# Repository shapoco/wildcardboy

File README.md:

# [WIP] WildCardBoy

Handheld Game Console with Replaceable MCU

## Concept

WildCardBoy is a handheld game console whose "brain" (MCU) can be swapped out.
It consists of two units:

- **Host shell**: The main unit with an LCD, keypad, TF card slot, and power supply.
  It has no game-execution capability of its own; instead, it has a slot for a logic card on its back.
- **Logic card**: A daughterboard that plugs into the slot. It carries the MCU that runs the game,
  along with the CPU peripheral circuitry of the target game console (e.g. TinyJoypad, Arduboy).

The differences between game consoles are confined to the logic card,
so supporting a new game console only requires building a new logic card.

The host shell acts as an RP2350B-based host controller with the following roles:

- Detecting the logic card and identifying its type via the on-card EEPROM (card profile)
- Reading keypad input and sending it to the logic card
- Driving the LCD based on drawing commands received from the logic card
- Flashing game programs stored on the TF card to the MCU on the logic card

For detailed specifications, see [spec/](spec/).

For demos and the latest development status, see the [#WildCardBoy tag on X](https://x.com/hashtag/WildCardBoy?f=live).

## Schematics

[host_shell.kicad_sch](https://kicanvas.org/?repo=https://github.com/shapoco/wildcardboy/blob/main/kicad/host_shell.kicad_sch)

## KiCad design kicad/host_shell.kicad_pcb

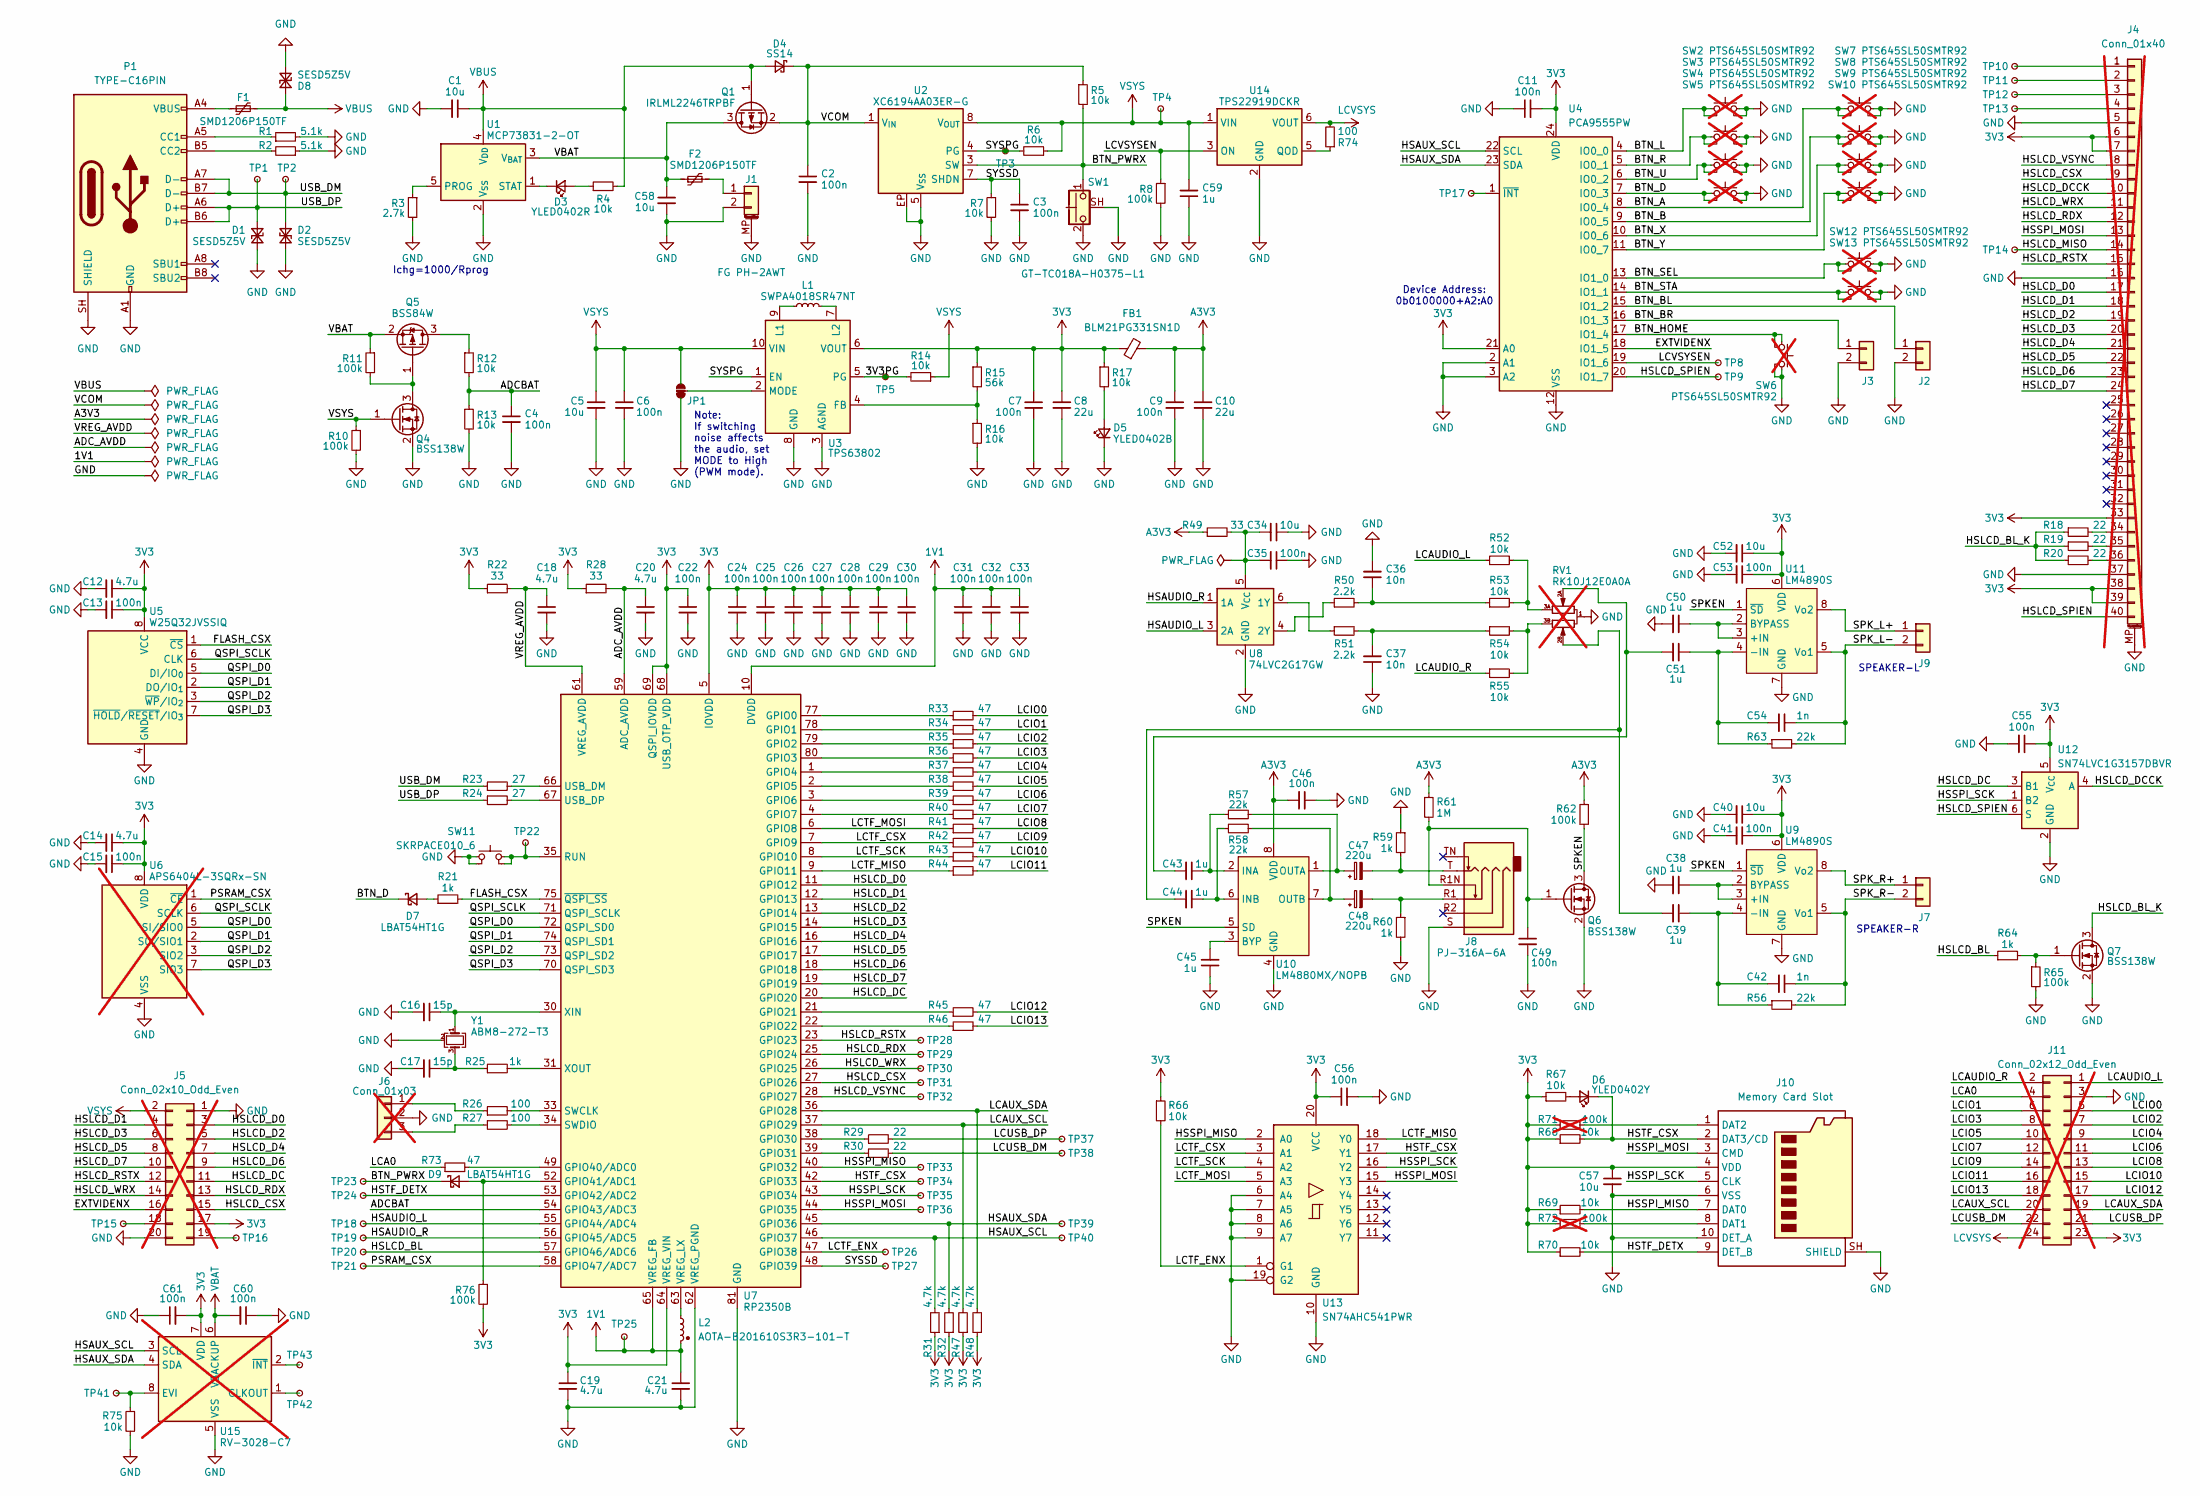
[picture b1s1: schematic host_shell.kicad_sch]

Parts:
C1, C5, C34, C40, C52, C57, C58: 10u; C_0603_1608Metric; LCSC C1691
C2, C3, C4, C6, C7, C9, C11, C13, C15, C22, C24, C25, C26, C27, C28, C29, C30, C31, C32, C33, C35, C41, C46, C49, C53, C55, C56, C60, C61: 100n; C_0402_1005Metric; LCSC C1525
C8, C10: 22u; C_0603_1608Metric; LCSC C59461
C12, C14, C18, C19, C20, C21: 4.7u; C_0603_1608Metric; LCSC C19666
C16, C17: 15p; C_0402_1005Metric; LCSC C1548
C36, C37: 10n; C_0402_1005Metric; LCSC C15195
C38, C39, C43, C44, C45, C50, C51, C59: 1u; C_0402_1005Metric; LCSC C52923
C42, C54: 1n; C_0402_1005Metric; LCSC C1523
C47, C48: 220u; CP_Elec_6.3x5.4; LCSC C3345
D1, D2, D8: SESD5Z5V; D_SOD-523; LCSC C19631222
D3: YLED0402R; LED_0402_1005Metric_Pad0.77x0.64mm_HandSolder; LCSC C21260817
D4: SS14; D_SMA; LCSC C2480
D5: YLED0402B; LED_0402_1005Metric_Pad0.77x0.64mm_HandSolder; LCSC C30584803
D6: YLED0402Y; LED_0402_1005Metric_Pad0.77x0.64mm_HandSolder; LCSC C20608782
D7, D9: LBAT54HT1G; D_SOD-323; LCSC C12744
F1, F2: SMD1206P150TF; Fuse_1206_3216Metric; LCSC C20802
FB1: BLM21PG331SN1D; L_0805_2012Metric; LCSC C74764
J1: FG PH-2AWT; JST_PH_S2B-PH-SM4-TB_1x02-1MP_P2.00mm_Horizontal; LCSC C2763693
J2, J3: Conn_01x02; SolderWirePad_1x02_SMD_2.5x1.5mm
J4: Conn_01x40; FFC_Conn_40P_Top_Hand; not fitted
J5: Conn_02x10_Odd_Even; PinSocket_2x10_P2.54mm_Horizontal; not fitted
J6: Conn_01x03; PinHeader_1x03_P2.54mm_Vertical; not fitted
J7, J9: Conn_01x02; SolderWirePad_2x01_SMD_2.5x1.5mm
J8: PJ-316A-6A; Jack_3.5mm_PJ-316A-6A_Horizontal; LCSC C128987
J10: Memory Card Slot; microSD_HC_Hirose_DM3AT-SF-PEJM5; LCSC C114218
J11: Conn_02x12_Odd_Even; PinSocket_2x12_P2.54mm_Horizontal; not fitted
JP1: SolderJumper_3_Bridged12; SolderJumper-3_P1.3mm_Bridged12_RoundedPad1.0x1.5mm
L1: SWPA4018SR47NT; L_Sunlord_SWPA4018S; LCSC C527613
L2: AOTA-B201610S3R3-101-T; LCSC C42411119
P1: TYPE-C16PIN; USB_C_Receptacle_HCTL_HC-TYPE-C-16P-01A; LCSC C393939
Q1: IRLML2246TRPBF; SOT-23; LCSC C127272
Q4, Q6, Q7: BSS138W; SOT-323_SC-70; LCSC C504052
Q5: BSS84W; SOT-323_SC-70; LCSC C919394
R1, R2: 5.1k; R_0402_1005Metric; LCSC C25905
R3: 2.7k; R_0402_1005Metric; LCSC C25885
R4, R5, R6, R7, R12, R13, R14, R16, R17, R52, R53, R54, R55, R66, R67, R68, R69, R70, R75: 10k; R_0402_1005Metric; LCSC C25744
R8, R10, R11, R62, R65, R76: 100k; R_0402_1005Metric; LCSC C25741
R15: 56k; R_0402_1005Metric; LCSC C25567
R18, R19, R20, R29, R30: 22; R_0402_1005Metric; LCSC C25092
R21, R25, R59, R60, R64: 1k; R_0402_1005Metric; LCSC C11702
R22, R28, R49: 33; R_0402_1005Metric; LCSC C25105
R23, R24: 27; R_0402_1005Metric; LCSC C25100
R26, R27, R74: 100; R_0402_1005Metric; LCSC C25076
R31, R32, R47, R48: 4.7k; R_0402_1005Metric; LCSC C25900
R33, R34, R35, R36, R37, R38, R39, R40, R41, R42, R43, R44, R45, R46, R73: 47; R_0402_1005Metric; LCSC C25118
R50, R51: 2.2k; R_0402_1005Metric; LCSC C25879
R56, R57, R58, R63: 22k; R_0402_1005Metric; LCSC C25768
R61: 1M; R_0402_1005Metric; LCSC C26083
R71, R72: 100k; R_0402_1005Metric; LCSC C25741; not fitted
RV1: RK10J12E0A0A; RK10J1xE; LCSC C351176; not fitted
SW1: GT-TC018A-H0375-L1; LCSC C963235
SW2, SW3, SW4, SW5, SW6, SW7, SW8, SW9, SW10, SW12, SW13: PTS645SL50SMTR92; SW_SPST_PTS645Sx43SMTR92; not fitted
SW11: SKRPACE010_6; SW_Push_1P1T_NO_Vertical_Wuerth_434133025816; LCSC C139797
TP1, TP2, TP3, TP4, TP5, TP8, TP9, TP10, TP11, TP12, TP13, TP14, TP15, TP16, TP17, TP18, TP19, TP20, TP21, TP22, TP23, TP24, TP25, TP26, TP27, TP28, TP29, TP30, TP31, TP32, TP33, TP34, TP35, TP36, TP37, TP38, TP39, TP40, TP41, TP42, TP43: TestPoint_Small; TestPoint_Pad_D1.0mm
U1: MCP73831-2-OT; SOT-23-5; LCSC C14879
U2: XC6194AA03ER-G; USP-8B06; LCSC C18221112
U3: TPS63802; LCSC C2845237
U4: PCA9555PW; TSSOP-24_4.4x7.8mm_P0.65mm; LCSC C128392
U5: W25Q32JVSSIQ; SOIC-8_5.3x5.3mm_P1.27mm; LCSC C179173
U6: APS6404L-3SQRx-SN; SOP-8_3.76x4.96mm_P1.27mm; not fitted
U7: RP2350B; QFN-80-1EP_10x10mm_P0.4mm_EP3.4x3.4mm; LCSC C42415655
U8: 74LVC2G17GW; SOT-363_SC-70-6; LCSC C19829576
U9, U11: LM4890S; MSOP-8_3x3mm_P0.65mm; LCSC C329452
U10: LM4880MX/NOPB; SOIC-8_3.9x4.9mm_P1.27mm; LCSC C2872533
U12: SN74LVC1G3157DBVR; SOT-23-6; LCSC C10426
U13: SN74AHC541PWR; TSSOP-20_4.4x6.5mm_P0.65mm; LCSC C406865
U14: TPS22919DCKR; SOT-363_SC-70-6; LCSC C2149796
U15: RV-3028-C7; MicroCrystal_C7_SON-8_1.5x3.2mm_P0.9mm; LCSC C3304278; not fitted
Y1: ABM8-272-T3; Crystal_SMD_3225-4Pin_3.2x2.5mm; LCSC C20625731

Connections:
1V1: C21.1, C31.1, C32.1, C33.1, L2.1, TP25.1 (1_1), U7.10 (DVDD), U7.32 (DVDD), U7.51 (DVDD), U7.65 (VREG_FB)
3V3: C7.1, C8.1, C11.2, C12.1, C13.1, C14.1, C15.1, C19.1, C22.1, C24.1, C25.1, C26.1, C27.1, C28.1, C29.1, C30.1, C40.1, C41.1, C52.1, C53.1, C55.1, C56.1, C57.1, C61.2, FB1.1, J4.6, J4.7, J4.33, J4.38, J4.39, J5.17, J10.4 (VDD), J11.23, R15.1, R17.1, R22.1, R28.1, R31.1, R32.1, R47.1, R48.1, R66.1, R67.1, R68.1, R69.1, R70.1, R71.1, R72.1, R76.2, U3.6 (VOUT), U4.21 (A0), U4.24 (VDD), U5.8 (VCC), U6.8 (VDD), U7.5 (IOVDD), U7.15 (IOVDD), U7.24 (IOVDD), U7.29 (IOVDD), U7.41 (IOVDD), U7.50 (IOVDD), U7.60 (IOVDD), U7.64 (VREG_VIN), U7.68 (USB_OTP_VDD), U7.69 (QSPI_IOVDD), U7.76 (IOVDD), U9.6 (VDD), U11.6 (VDD), U12.5 (V_{CC}), U13.20 (VCC), U15.7 (VDD)
/3V3PG: R14.2, TP5.1 (1_1), U3.5 (PG)
/ADCBAT: C4.1, R12.2, R13.1, U7.54 (GPIO43/ADC3)
/ADC_AVDD: C20.1, R28.2, U7.59 (ADC_AVDD)
/BTN_A: SW7.1, U4.8 (IO0_4)
/BTN_B: SW8.1, U4.9 (IO0_5)
/BTN_BL: J2.1, U4.15 (IO1_2)
/BTN_BR: J3.1, U4.16 (IO1_3)
/BTN_D: D7.1 (K), SW5.1, U4.7 (IO0_3)
/BTN_HOME: SW6.1, U4.17 (IO1_4)
/BTN_L: SW2.1, U4.4 (IO0_0)
/BTN_PWRX: D9.1 (K), R5.2, SW1.1, TP23.1 (1_1), U2.3 (SW)
/BTN_R: SW3.1, U4.5 (IO0_1)
/BTN_SEL: SW12.1, U4.13 (IO1_0)
/BTN_STA: SW13.1, U4.14 (IO1_1)
/BTN_U: SW4.1, U4.6 (IO0_2)
/BTN_X: SW9.1, U4.10 (IO0_6)
/BTN_Y: SW10.1, U4.11 (IO0_7)
/EXTVIDENX: J5.16, U4.18 (IO1_5)
/FLASH_CSX: R21.2, U5.1 (~CS), U7.75 (~QSPI_SS)
/HSAUDIO_L: TP18.1 (1_1), U7.55 (GPIO44/ADC4), U8.3 (2A)
/HSAUDIO_R: TP19.1 (1_1), U7.56 (GPIO45/ADC5), U8.1 (1A)
/HSAUX_SCL: R31.2, TP40.1 (1_1), U4.22 (SCL), U7.46 (GPIO37), U15.3 (SCL)
/HSAUX_SDA: R32.2, TP39.1 (1_1), U4.23 (SDA), U7.45 (GPIO36), U15.4 (SDA)
/HSLCD_BL: R64.1, TP20.1 (1_1), U7.57 (GPIO46/ADC6)
/HSLCD_BL_K: Q7.3 (D), R18.1, R19.1, R20.1
/HSLCD_CSX: J4.9, J5.15, TP31.1 (1_1), U7.27 (GPIO26)
/HSLCD_D0: J4.17, J5.3, U7.11 (GPIO12)
/HSLCD_D1: J4.18, J5.4, U7.12 (GPIO13)
/HSLCD_D2: J4.19, J5.5, U7.13 (GPIO14)
/HSLCD_D3: J4.20, J5.6, U7.14 (GPIO15)
/HSLCD_D4: J4.21, J5.7, U7.16 (GPIO16)
/HSLCD_D5: J4.22, J5.8, U7.17 (GPIO17)
/HSLCD_D6: J4.23, J5.9, U7.18 (GPIO18)
/HSLCD_D7: J4.24, J5.10, U7.19 (GPIO19)
/HSLCD_DC: J5.11, U7.20 (GPIO20), U12.3 (B1)
/HSLCD_DCCK: J4.10, U12.4 (A)
/HSLCD_MISO: J4.14, TP14.1 (1_1)
/HSLCD_RDX: J4.12, J5.13, TP29.1 (1_1), U7.25 (GPIO24)
/HSLCD_RSTX: J4.15, J5.12, TP28.1 (1_1), U7.23 (GPIO23)
/HSLCD_SPIEN: J4.40, TP9.1 (1_1), U4.20 (IO1_7), U12.6 (S)
/HSLCD_VSYNC: J4.8, TP32.1 (1_1), U7.28 (GPIO27)
/HSLCD_WRX: J4.11, J5.14, TP30.1 (1_1), U7.26 (GPIO25)
/HSSPI_MISO: J10.7 (DAT0), R69.2, TP33.1 (1_1), U7.40 (GPIO32), U13.2 (A0)
/HSSPI_MOSI: J4.13, J10.3 (CMD), TP36.1 (1_1), U7.44 (GPIO35), U13.15 (Y3)
/HSSPI_SCK: J10.5 (CLK), TP35.1 (1_1), U7.43 (GPIO34), U12.1 (B2), U13.16 (Y2)
/HSTF_CSX: D6.1 (K), J10.2 (DAT3/CD), R68.2, TP34.1 (1_1), U7.42 (GPIO33), U13.17 (Y1)
/HSTF_DETX: J10.9 (DET_B), R70.2, TP24.1 (1_1), U7.53 (GPIO42/ADC2)
/LCA0: J11.4, R73.1
/LCAUDIO_L: J11.1, R52.1
/LCAUDIO_R: J11.2, R55.1
/LCAUX_SCL: J11.20, R47.2, U7.37 (GPIO29)
/LCAUX_SDA: J11.19, R48.2, U7.36 (GPIO28)
/LCIO0: J11.5, R33.2
/LCIO1: J11.6, R34.2
/LCIO2: J11.7, R35.2
/LCIO3: J11.8, R36.2
/LCIO4: J11.9, R37.2
/LCIO5: J11.10, R38.2
/LCIO6: J11.11, R39.2
/LCIO7: J11.12, R40.2
/LCIO8: J11.13, R41.2
/LCIO9: J11.14, R42.2
/LCIO10: J11.15, R43.2
/LCIO11: J11.16, R44.2
/LCIO12: J11.17, R45.2
/LCIO13: J11.18, R46.2
/LCTF_CSX: R42.1, U7.7 (GPIO9), U13.3 (A1)
/LCTF_ENX: R66.2, TP26.1 (1_1), U7.47 (GPIO38), U13.1 (G1)
/LCTF_MISO: R44.1, U7.9 (GPIO11), U13.18 (Y0)
/LCTF_MOSI: R41.1, U7.6 (GPIO8), U13.5 (A3)
/LCTF_SCK: R43.1, U7.8 (GPIO10), U13.4 (A2)
/LCUSB_DM: J11.22, R30.2, TP38.1 (1_1)
/LCUSB_DP: J11.21, R29.2, TP37.1 (1_1)
/LCVSYSEN: R8.1, TP8.1 (1_1), U4.19 (IO1_6), U14.3 (ON)
/PSRAM_CSX: TP21.1 (1_1), U6.1 (~CE), U7.58 (GPIO47/ADC7)
/QSPI_D0: U5.5 (DI/IO_{0}), U6.5 (SI/SIO0), U7.72 (QSPI_SD0)
/QSPI_D1: U5.2 (DO/IO_{1}), U6.2 (SO/SIO1), U7.74 (QSPI_SD1)
/QSPI_D2: U5.3 (~WP/IO_{2}), U6.3 (SIO2), U7.73 (QSPI_SD2)
/QSPI_D3: U5.7 (~HOLD/~RESET/IO_{3}), U6.7 (SIO3), U7.70 (QSPI_SD3)
/QSPI_SCLK: U5.6 (CLK), U6.6 (SCLK), U7.71 (QSPI_SCLK)
/SPKEN: Q6.3 (D), R62.2, U9.1 (~SD), U10.5 (SD), U11.1 (~SD)
/SPK_L+: J9.1, U11.8 (Vo2)
/SPK_L-: C54.1, J9.2, R63.2, U11.5 (Vo1)
/SPK_R+: J7.1, U9.8 (Vo2)
/SPK_R-: C42.1, J7.2, R56.2, U9.5 (Vo1)
/SYSPG: R6.2, TP3.1 (1_1), U2.4 (PG), U3.1 (EN)
/SYSSD: C3.1, R7.1, TP27.1 (1_1), U2.7 (SHDN), U7.48 (GPIO39)
/USB_DM: D2.1 (A1), P1.A7 (D-), P1.B7 (D-), R23.1, TP2.1 (1_1)
/USB_DP: D1.1 (A1), P1.A6 (D+), P1.B6 (D+), R24.1, TP1.1 (1_1)
/VCOM: C2.1, D4.1 (K), Q1.2 (S), R5.1, U2.1 (V_{IN})
/VREG_AVDD: C18.1, R22.2, U7.61 (VREG_AVDD)
A3V3: C9.1, C10.1, C46.2, FB1.2, R49.1, R61.1, R62.1, U10.8 (VDD)
GND: C1.2, C2.2, C3.2, C4.2, C5.2, C6.2, C7.2, C8.2, C9.2, C10.2, C11.1, C12.2, C13.2, C14.2, C15.2, C16.2, C17.2, C18.2, C19.2, C20.2, C21.2, C22.2, C24.2, C25.2, C26.2, C27.2, C28.2, C29.2, C30.2, C31.2, C32.2, C33.2, C34.1, C35.1, C36.2, C37.1, C38.2, C40.2, C41.2, C45.1, C46.1, C49.2, C50.2, C52.2, C53.2, C55.2, C56.2, C57.2, C58.2, C59.1, C60.1, C61.1, D1.2 (A2), D2.2 (A2), D5.1 (K), D8.2 (A2), J1.2, J1.MP (MountPin), J2.2, J3.2, J4.5, J4.16, J4.37, J4.MP (MountPin), J5.1, J5.20, J6.2, J8.S, J10.6 (VSS), J10.10 (DET_A), J10.SH (SHIELD), J11.3, JP1.1 (A), P1.A1 (GND), P1.A12 (GND), P1.B1 (GND), P1.B12 (GND), P1.SH (SHIELD), Q4.2 (S), Q6.2 (S), Q7.2 (S), R1.2, R2.1, R3.2, R7.2, R8.2, R10.2, R13.2, R16.2, R59.1, R60.2, R65.2, R75.2, RV1.1, SW1.2, SW1.SH (B), SW2.2, SW3.2, SW4.2, SW5.2, SW6.2, SW7.2, SW8.2, SW9.2, SW10.2, SW11.1, SW12.2, SW13.2, U1.2 (V_{SS}), U2.5 (V_{SS}), U2.EP, U3.3 (AGND), U3.8 (GND), U4.2 (A1), U4.3 (A2), U4.12 (VSS), U5.4 (GND), U6.4 (VSS), U7.62 (VREG_PGND), U7.81 (GND), U8.2 (GND), U9.7 (GND), U10.4 (GND), U11.7 (GND), U12.2 (GND), U13.6 (A4), U13.7 (A5), U13.8 (A6), U13.9 (A7), U13.10 (GND), U13.19 (G2), U14.2 (GND), U15.5 (VSS), Y1.2 (G), Y1.4 (G)
LCVSYS: J11.24, R74.2, U14.6 (VOUT)
unnamed: C17.1, R25.1, Y1.3
unnamed: C36.1, R50.2, R53.1
unnamed: C37.2, R51.2, R54.1
unnamed: C39.2, C44.2, RV1.2B
unnamed: C43.2, C51.2, RV1.2A
unnamed: C47.2, J8.T, R59.2
unnamed: C48.2, J8.R1, R60.1
unnamed: D3.2 (A), R4.1
unnamed: D3.1 (K), U1.1 (STAT)
unnamed: D5.2 (A), R17.2
unnamed: D6.2 (A), R67.2
unnamed: D7.2 (A), R21.1
unnamed: D9.2 (A), R76.1, U7.52 (GPIO41/ADC1)
unnamed: F1.1, P1.A4 (VBUS), P1.A9 (VBUS), P1.B4 (VBUS), P1.B9 (VBUS)
unnamed: F2.2, J1.1
unnamed: J4.1, TP10.1 (1_1)
unnamed: J4.2, TP11.1 (1_1)
unnamed: J4.3, TP12.1 (1_1)
unnamed: J4.4, TP13.1 (1_1)
unnamed: J4.34, R18.2
unnamed: J4.35, R19.2
unnamed: J4.36, R20.2
unnamed: J5.18, TP15.1 (1_1)
unnamed: J5.19, TP16.1 (1_1)
unnamed: J6.1, R26.1
unnamed: J6.3, R27.1
unnamed: J10.8 (DAT1), R72.2
unnamed: J10.1 (DAT2), R71.2
unnamed: JP1.2 (C), U3.2 (MODE)
unnamed: P1.A5 (CC1), R1.1
unnamed: P1.B5 (CC2), R2.2
unnamed: Q4.3 (D), Q5.1 (G), R11.2
unnamed: Q5.3 (D), R12.1
unnamed: C49.1, J8.R1N, Q6.1 (G), R61.2
unnamed: Q7.1 (G), R64.2, R65.1
unnamed: R52.2, R53.2, RV1.3A
unnamed: R54.2, R55.2, RV1.3B
unnamed: R3.1, U1.5 (PROG)
unnamed: R15.2, R16.1, U3.4 (FB)
unnamed: L1.2, U3.9 (L1)
unnamed: L1.1, U3.7 (L2)
unnamed: TP17.1 (1_1), U4.1 (~INT)
unnamed: R33.1, U7.77 (GPIO0)
unnamed: R34.1, U7.78 (GPIO1)
unnamed: R35.1, U7.79 (GPIO2)
unnamed: R36.1, U7.80 (GPIO3)
unnamed: R37.1, U7.1 (GPIO4)
unnamed: R38.1, U7.2 (GPIO5)
unnamed: R39.1, U7.3 (GPIO6)
unnamed: R40.1, U7.4 (GPIO7)
unnamed: R45.1, U7.21 (GPIO21)
unnamed: R46.1, U7.22 (GPIO22)
unnamed: R29.1, U7.38 (GPIO30)
unnamed: R30.1, U7.39 (GPIO31)
unnamed: R73.2, U7.49 (GPIO40/ADC0)
unnamed: SW11.2, TP22.1 (1_1), U7.35 (RUN)
unnamed: R26.2, U7.33 (SWCLK)
unnamed: R27.2, U7.34 (SWDIO)
unnamed: R23.2, U7.66 (USB_DM)
unnamed: R24.2, U7.67 (USB_DP)
unnamed: L2.2, U7.63 (VREG_LX)
unnamed: C16.1, U7.30 (XIN), Y1.1
unnamed: R25.2, U7.31 (XOUT)
unnamed: R51.1, U8.6 (1Y)
unnamed: R50.1, U8.4 (2Y)
unnamed: C34.2, C35.2, R49.2, U8.5 (V_{CC})
unnamed: C38.1, U9.2 (BYPASS), U9.3 (+IN)
unnamed: C39.1, C42.2, R56.1, U9.4 (-IN)
unnamed: C45.2, U10.3 (BYP)
unnamed: C43.1, R57.1, U10.2 (INA)
unnamed: C44.1, R58.1, U10.6 (INB)
unnamed: C47.1, R57.2, U10.1 (OUTA)
unnamed: C48.1, R58.2, U10.7 (OUTB)
unnamed: C50.1, U11.2 (BYPASS), U11.3 (+IN)
unnamed: C51.1, C54.2, R63.1, U11.4 (-IN)
unnamed: R74.1, U14.5 (QOD)
unnamed: TP42.1 (1_1), U15.1 (CLKOUT)
unnamed: R75.1, TP41.1 (1_1), U15.8 (EVI)
unnamed: TP43.1 (1_1), U15.2 (~INT)
VBAT: C58.1, C60.2, F2.1, Q1.3 (D), Q5.2 (S), R11.1, U1.3 (V_{BAT}), U15.6 (VBACKUP)
VBUS: C1.1, D4.2 (A), D8.1 (A1), F1.2, Q1.1 (G), R4.2, U1.4 (V_{DD})
VSYS: C5.1, C6.1, C59.2, J5.2, JP1.3 (B), Q4.1 (G), R6.1, R10.1, R14.1, TP4.1 (1_1), U2.8 (V_{OUT}), U3.10 (VIN), U14.1 (VIN)

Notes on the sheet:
SPEAKER-L
Note: If switching noise affects the audio, set MODE to High (PWM mode).
Ichg=1000/Rprog
Device Address: 0b0100000+A2:A0
SPEAKER-R

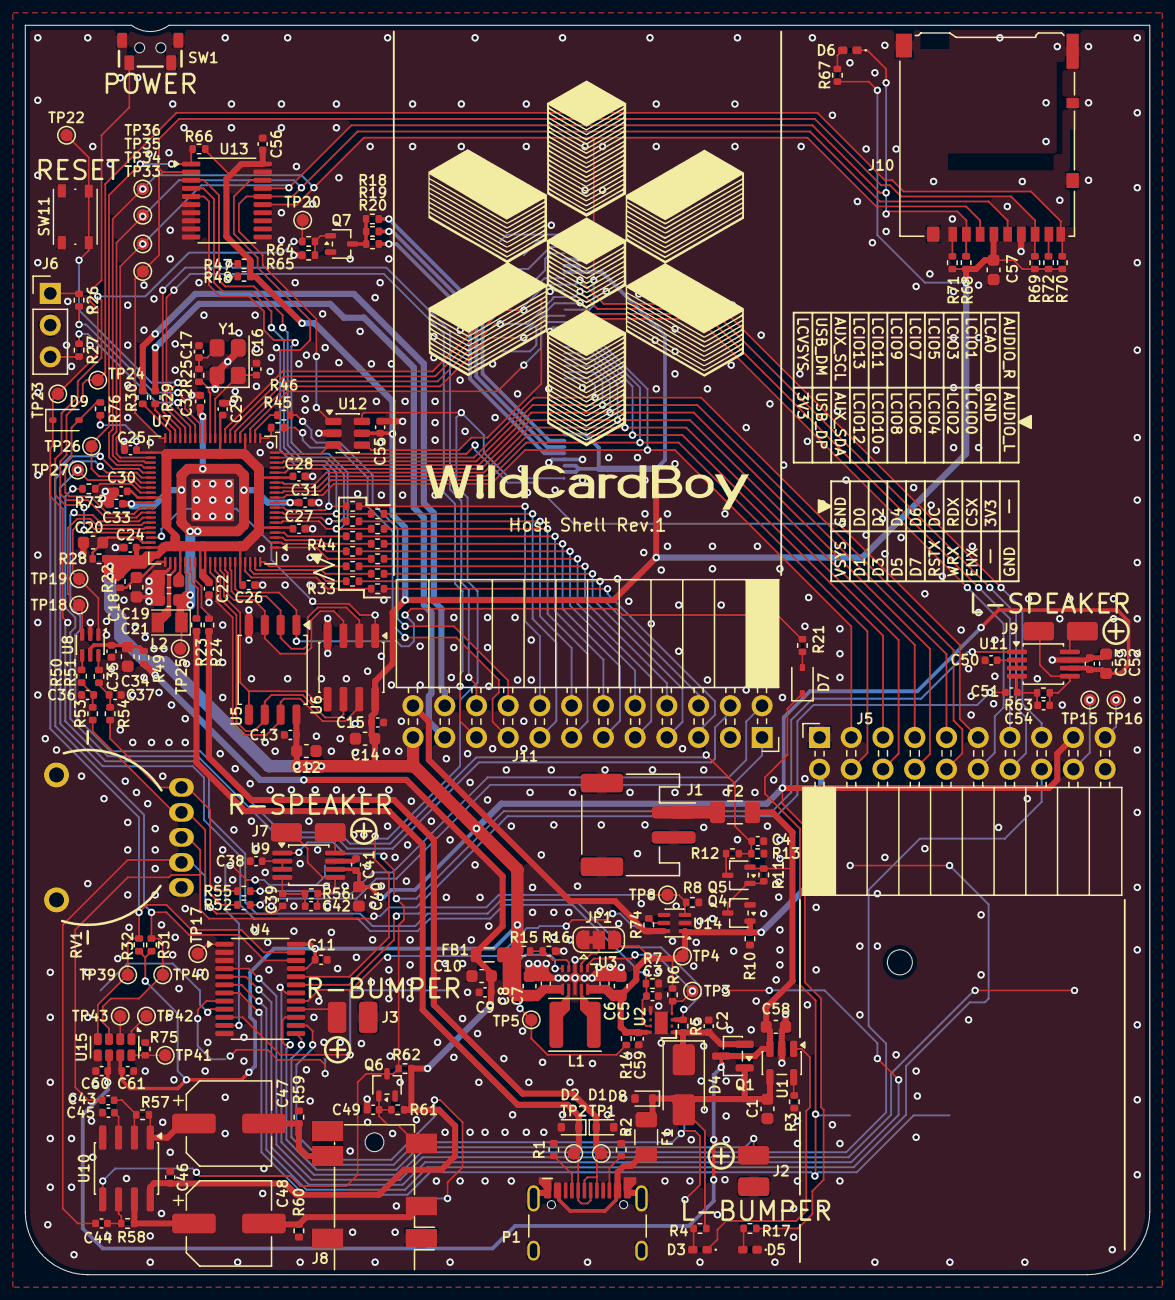
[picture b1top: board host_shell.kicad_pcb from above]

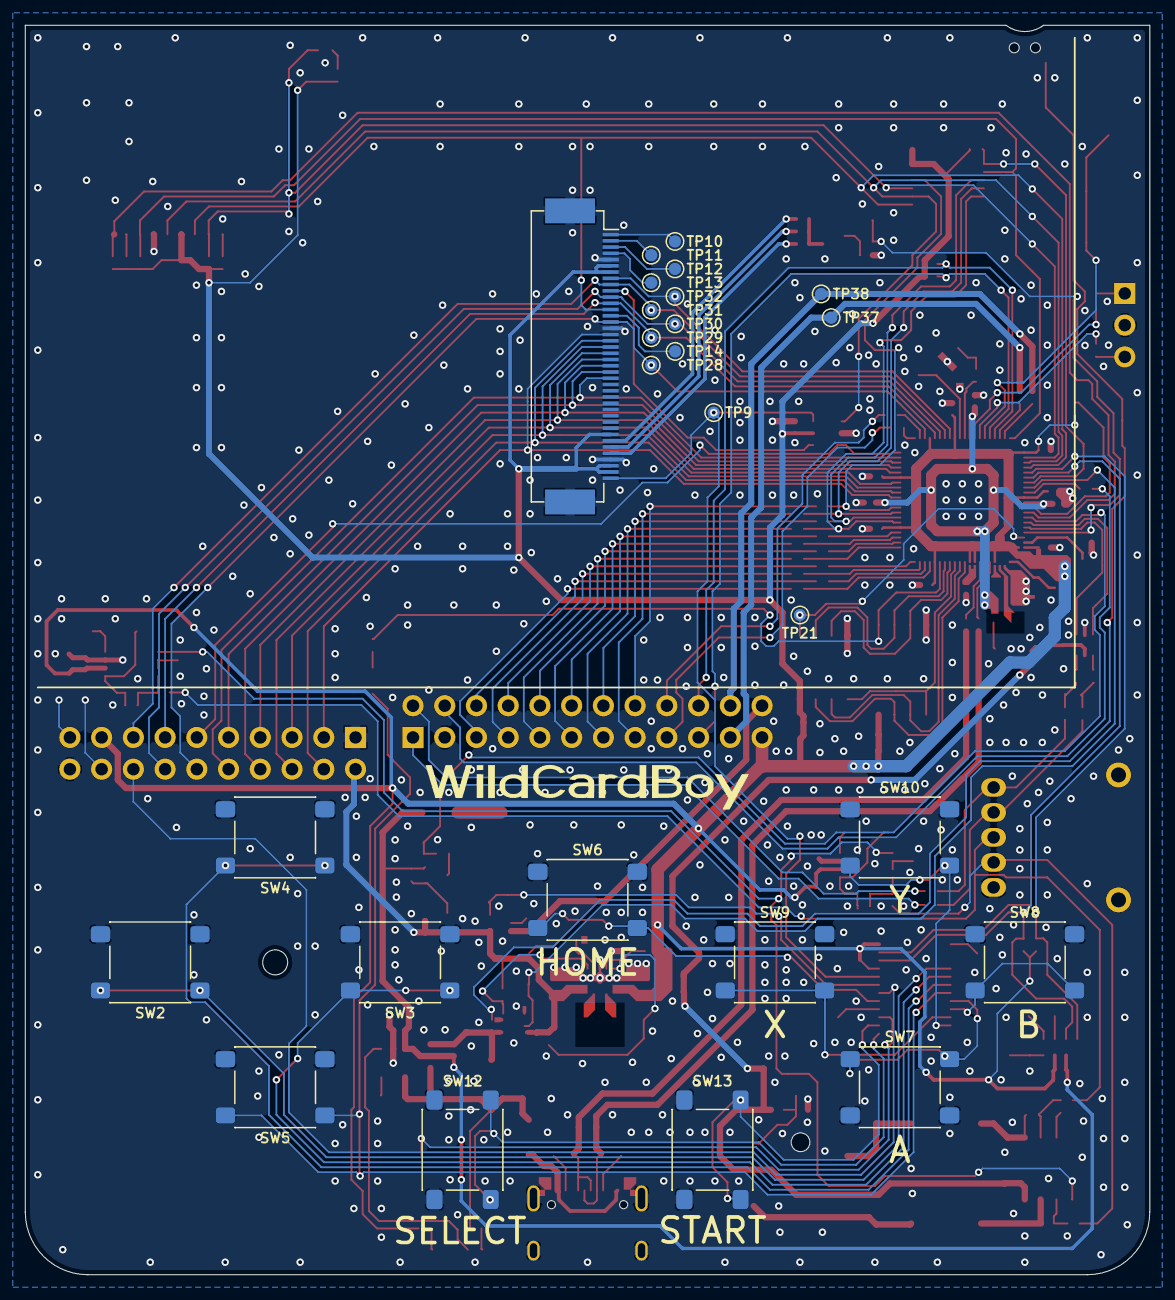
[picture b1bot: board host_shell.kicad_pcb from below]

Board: 2 copper layers, 90.0 x 100.0 mm, 238 parts (26 on the bottom side), 178 nets.

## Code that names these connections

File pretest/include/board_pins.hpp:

#pragma once

// WildCardBoy host controller pin map (see spec/01_host_interfaces.md, spec/02_wildcardbus.md) and constants shared by
// the pretest firmware.

#include <cstdint>

namespace wcb {

//-----------------------------------------------------------------------------
// Host LCD (ILI9488, 8080 8-bit parallel)
//-----------------------------------------------------------------------------
static constexpr uint PIN_LCD_RST = 15;
static constexpr uint PIN_LCD_D0 = 16;  // D0..D7 = GPIO16..23 (contiguous)
static constexpr uint PIN_LCD_DC = 24;
static constexpr uint PIN_LCD_WR = 25;  // NOTE: also PICO_DEFAULT_LED_PIN
static constexpr uint PIN_LCD_RD = 26;
static constexpr uint PIN_LCD_CS = 27;

// Logical (landscape) size. The panel is 320x480 portrait, rotated via MADCTL.
static constexpr uint16_t LCD_WIDTH = 480;
static constexpr uint16_t LCD_HEIGHT = 320;

//-----------------------------------------------------------------------------
// TF card (SPI0 pin group) and the TF card mux
//-----------------------------------------------------------------------------
static constexpr uint PIN_HTF_MISO = 32;  // SPI0 RX
static constexpr uint PIN_HTF_CS = 33;    // GPIO-controlled
static constexpr uint PIN_HTF_SCK = 34;   // SPI0 SCK
static constexpr uint PIN_HTF_MOSI = 35;  // SPI0 TX
// Low = TF card wired to the logic card, High = to the host controller.
// Pulled up on the board. While Low the HTF_* pins must be Hi-Z.
static constexpr uint PIN_LCTF_ENAX = 38;

//-----------------------------------------------------------------------------
// AUX I2C buses. Both pin pairs map to the I2C0 controller (GPIO % 4 == 0/1),
// so exactly one pair is switched to the I2C function at a time; the idle
// pair sits Hi-Z. This keeps card hot-plug glitches on LCAUX away from the
// host bus (HAUX).
//-----------------------------------------------------------------------------
// HAUX: host-side devices (keypad PCA9555).
static constexpr uint PIN_HAUX_SDA = 36;
static constexpr uint PIN_HAUX_SCL = 37;
// LCAUX: logic-card-side devices (ID EEPROM, card PCA9555 on other cards).
static constexpr uint PIN_LCAUX_SDA = 28;
static constexpr uint PIN_LCAUX_SCL = 29;
static constexpr uint32_t AUX_I2C_BAUD = 400 * 1000;

static constexpr uint8_t ADDR_HOST_KEYPAD = 0x21;  // PCA9555 (host, HAUX)
static constexpr uint8_t ADDR_CARD_KEYPAD = 0x20;  // PCA9555 (card, LCAUX) = LCIO32-47
static constexpr uint8_t ADDR_CARD_EEPROM = 0x50;  // 24LC256 (card, LCAUX)

// Host keypad bits as returned by PCA9555 (P0 = bits 0..7, P1 = bits 8..15).
// Inputs are active-low on the wire; hostKeysRead() returns them already
// inverted (1 = pressed).
static constexpr uint16_t HKEY_L = 1u << 0;
static constexpr uint16_t HKEY_R = 1u << 1;
static constexpr uint16_t HKEY_U = 1u << 2;
static constexpr uint16_t HKEY_D = 1u << 3;
static constexpr uint16_t HKEY_A = 1u << 4;
static constexpr uint16_t HKEY_B = 1u << 5;
static constexpr uint16_t HKEY_X = 1u << 6;
static constexpr uint16_t HKEY_Y = 1u << 7;
static constexpr uint16_t HKEY_STA = 1u << 8;
static constexpr uint16_t HKEY_SEL = 1u << 9;
static constexpr uint16_t HKEY_BL = 1u << 10;
static constexpr uint16_t HKEY_BR = 1u << 11;
static constexpr uint16_t HKEY_HOME = 1u << 12;

//-----------------------------------------------------------------------------
// WildCardBus
//-----------------------------------------------------------------------------
// LCIOn = GPIOn for n = 0..13. Which LCIO does what comes from the card
// profile (card_profile.hpp); only the LCD I2C pair is fixed by the spec.
static constexpr uint PIN_LCIO_BASE = 0;
static constexpr uint PIN_LC_LCD_SDA = 2;  // LCIO2 (I2C1 SDA)
static constexpr uint PIN_LC_LCD_SCL = 3;  // LCIO3 (I2C1 SCL)
// Virtual I/O expander bus (spec/02): the host is an i2c1 *slave* here.
// Mutually exclusive with the I2C LCD capture above (same controller).
static constexpr uint PIN_LCVIO_SDA = 6;  // LCIO6 (I2C1 SDA)
static constexpr uint PIN_LCVIO_SCL = 7;  // LCIO7 (I2C1 SCL)

// Logic card USB (PIO-USB host). DM must be DP + 1.
static constexpr uint PIN_LCUSB_DP = 30;
static constexpr uint PIN_LCUSB_DM = 31;

// PIO block assignment: pio0 = host LCD (8080), pio1 = PIO-USB host,
// pio2 = LcdTap SPI capture.
static constexpr uint PIO_USB_INDEX = 1;

// System clock (sys_clock.hpp). Peripheral dividers are derived from it.
// 312 MHz gives the LcdTap SPI capture more margin against the 62.5 MHz
// SCLK of PicoSystem cards (spi_4line_mode0.pio worst case = clk_sys / 4).
static constexpr uint32_t SYS_CLOCK_HZ = 312'000'000;

// TF card layout (see spec/05_tf_card.md).
static constexpr const char* CARDS_DIR = "/WCB/Cards";

}  // namespace wcb

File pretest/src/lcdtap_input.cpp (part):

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static constexpr uint32_t SPI_RING_WORDS = SPI_RING_BYTES / sizeof(uint32_t);
static constexpr uint32_t MAX_GROUPS_PER_CALL = 64;

// 4-line SPI pins: CS / SCLK are baked into spi_4line_mode0.pio (GPIO1 /
// GPIO2); MOSI and DC must be adjacent (IN_BASE, IN_BASE+1).
static constexpr uint PIN_SPI_RST = 0;
static constexpr uint PIN_SPI_CS = SPI_CS_PIN;      // 1
static constexpr uint PIN_SPI_SCLK = SPI_SCLK_PIN;  // 2
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static_assert(PIN_SPI_CS == 1 && PIN_SPI_SCLK == 2, "spi_4line_mode0.pio pin map");

// 8-bit parallel pins (WildCardBus fixed assignment, spec/02): CS / WR are
// baked into parallel_8bit.pio (GPIO1 / GPIO2), D0-7 = GPIO3-10 (IN_BASE),
// DC = GPIO11 (IN_BASE + 8). Cards with an on-board deserializer
// (PicoSystem) feed BCLK = SCLK/8 into WR.
static constexpr uint PIN_PAR_D0 = 3;
static constexpr uint PIN_PAR_DC = PIN_PAR_D0 + 8;  // 11
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    lcdtap::pico2::spiSlaveDeinit(&sSpi);
    sSpi.inst = nullptr;
    if (sBus == lcdtap::BusType::PARALLEL) {
      for (uint pin = PIN_SPI_RST; pin <= PIN_PAR_DC; ++pin) {  // LCIO0-11
        gpio_init(pin);
        gpio_disable_pulls(pin);
      }
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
